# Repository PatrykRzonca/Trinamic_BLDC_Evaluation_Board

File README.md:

# Trinamic_BLDC_Evaluation_Board
Project for evaluation board

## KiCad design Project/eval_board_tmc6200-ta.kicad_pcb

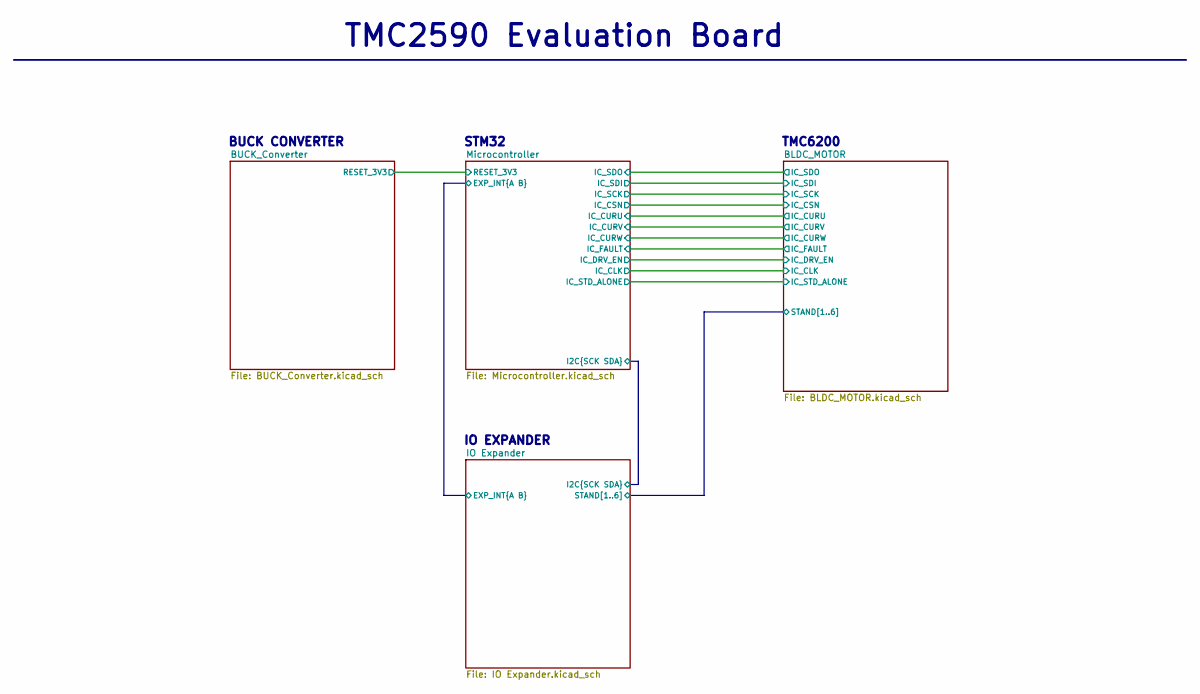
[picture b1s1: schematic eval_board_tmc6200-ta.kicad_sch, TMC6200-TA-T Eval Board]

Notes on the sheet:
BUCK CONVERTER
IO EXPANDER
TMC6200
STM32
TMC2590 Evaluation Board

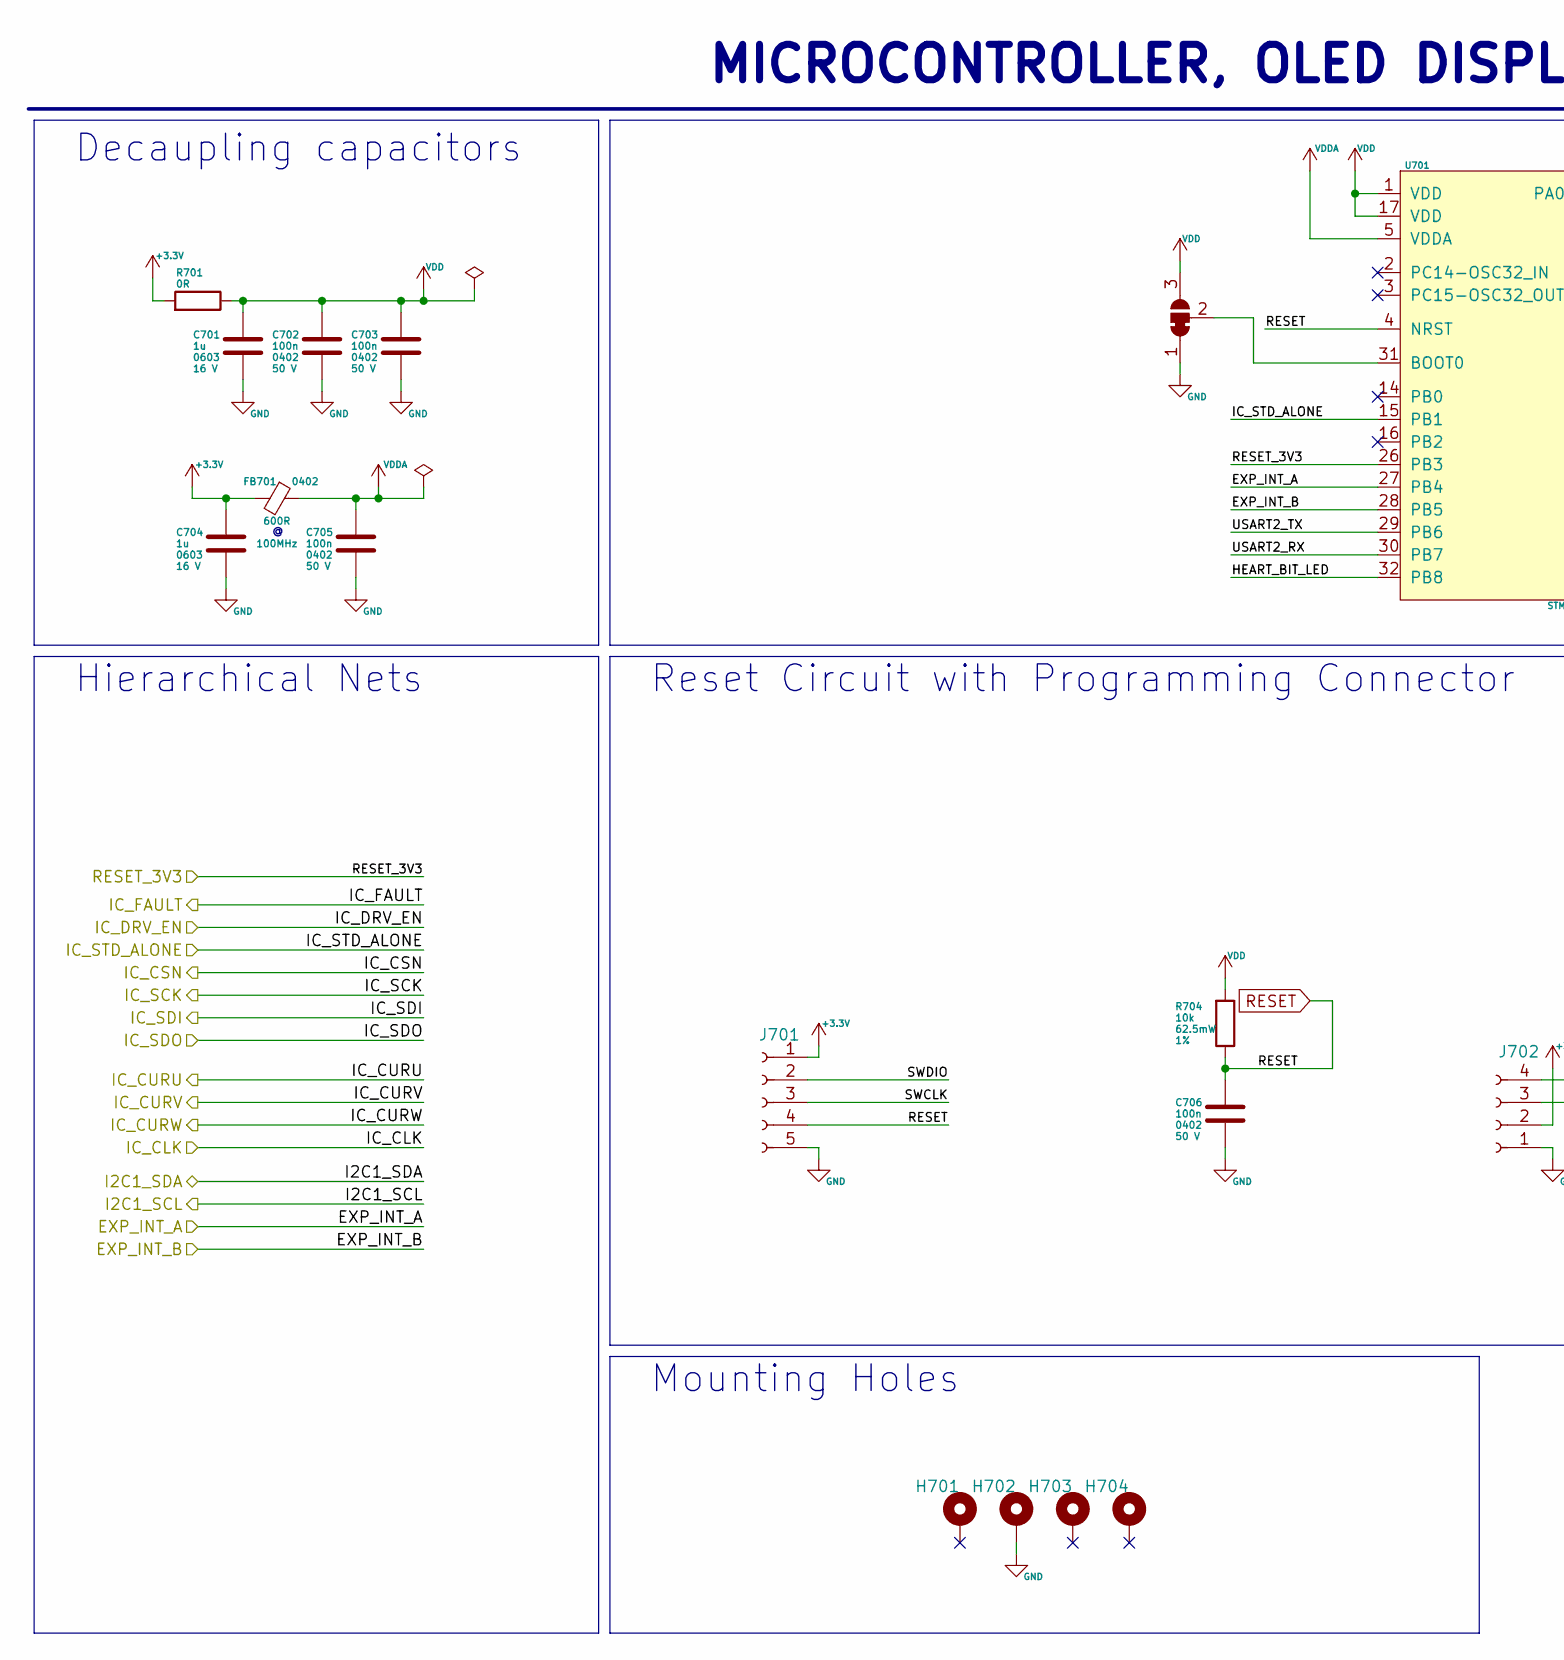
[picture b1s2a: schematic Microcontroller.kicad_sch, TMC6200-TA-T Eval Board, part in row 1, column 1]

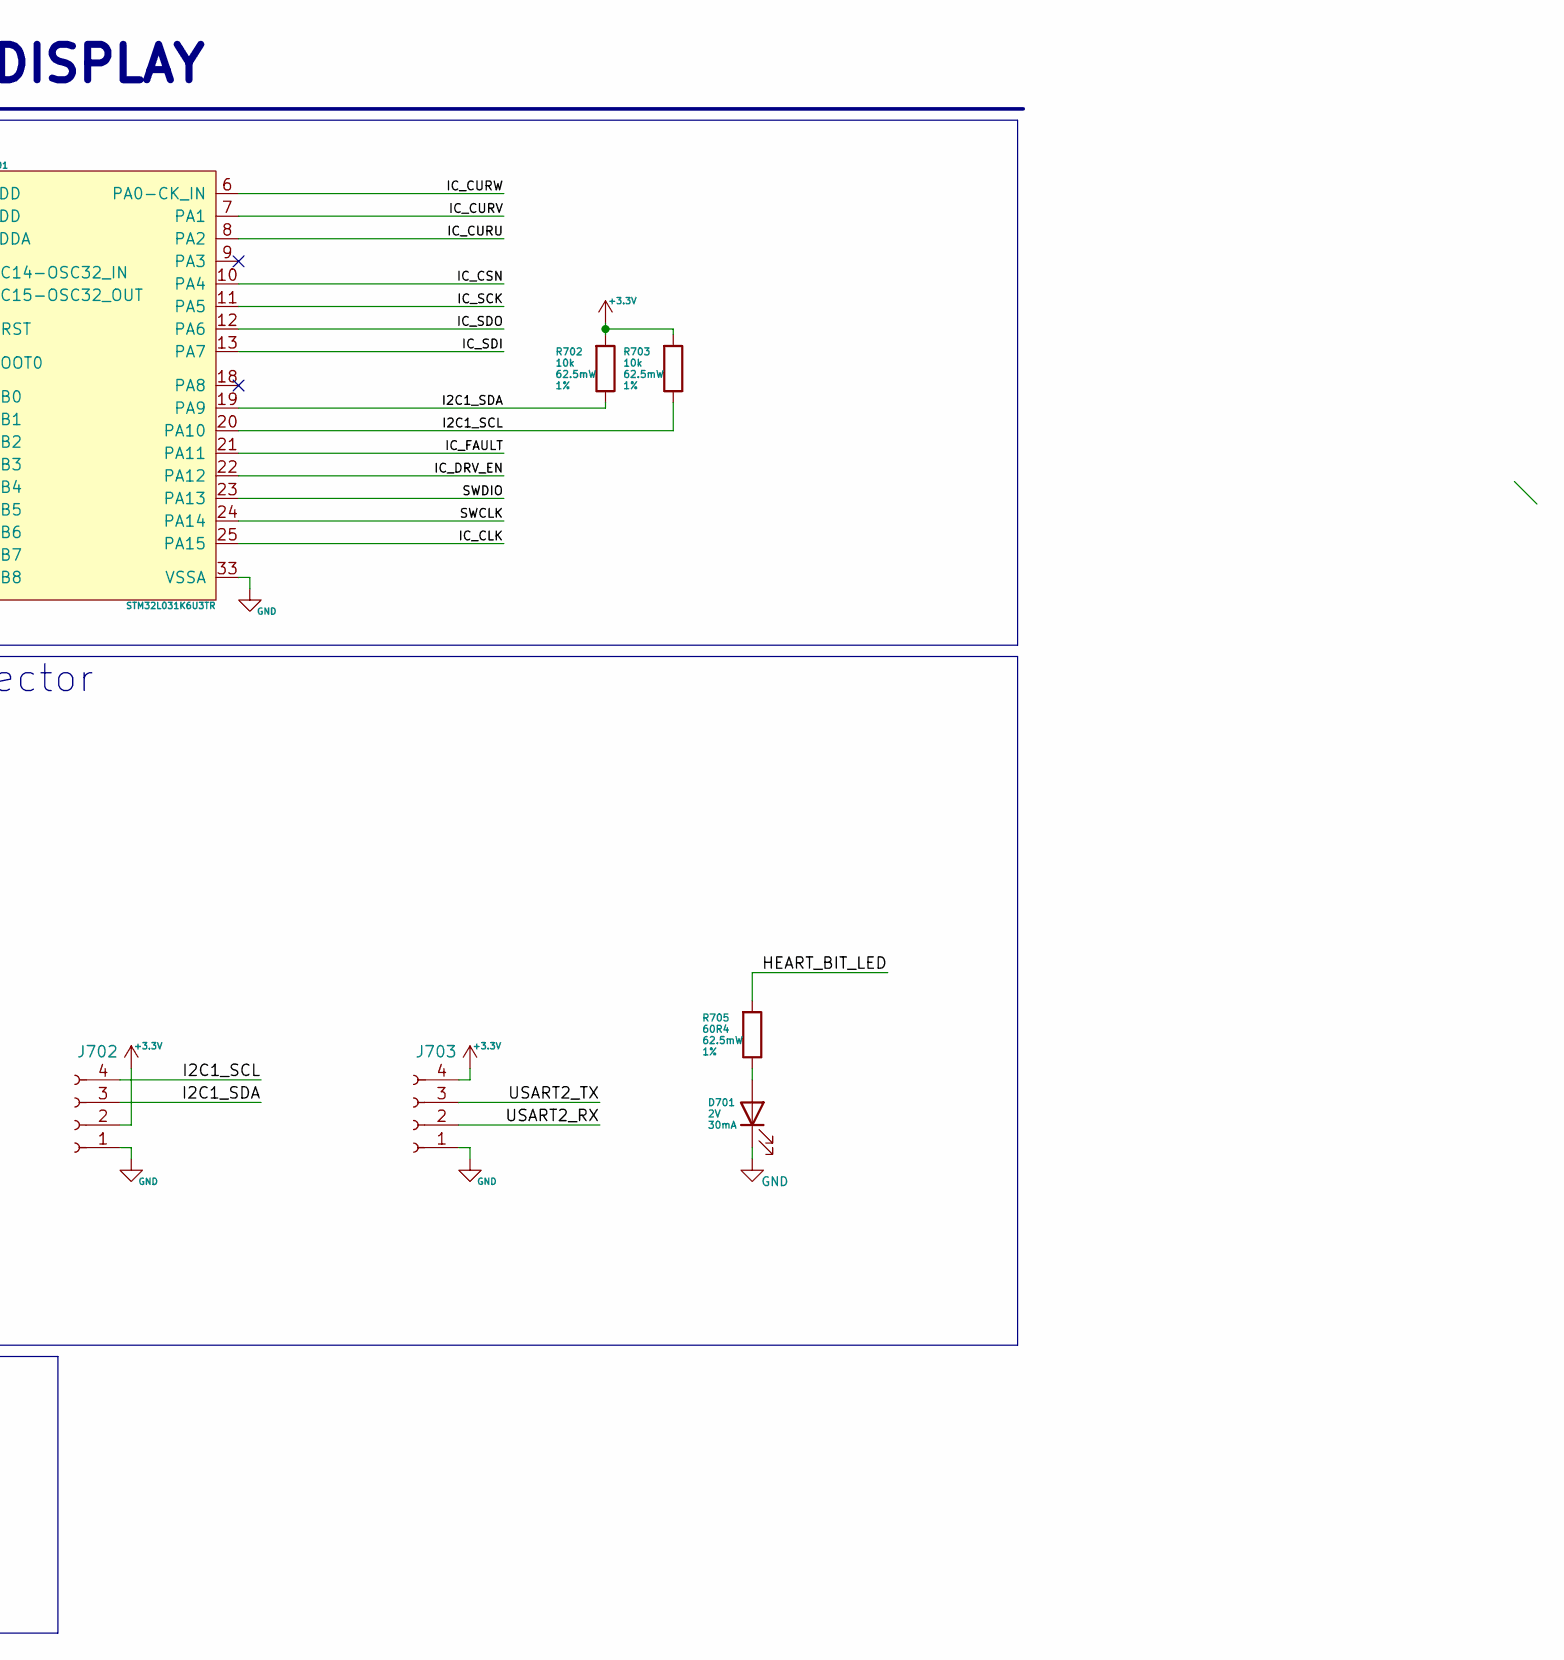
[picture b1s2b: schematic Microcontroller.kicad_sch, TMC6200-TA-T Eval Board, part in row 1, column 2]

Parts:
C701, C704: 1u; C_0603_1608Metric; Voltage 16 V; Tolerance 10 %; Part Number C0603C105K4RACTU
C702, C703, C705, C706: 100n; C_0402_1005Metric; Voltage 50 V; Tolerance 5%; Part Number GRM155C71H104JE19D
D701: LED; D_0402_1005Metric; Forward Voltage 2V; Part Number 150040VS73240
FB701: Ferrite_Bead; L_0402_1005Metric; Tolerance 25%; Part Number BLM15BD601SZ1D
H701, H702, H703, H704: MountingHole_Pad; MountingHole_2.7mm_M2.5_Pad_TopBottom
J701: Conn_01x05_Female; PinHeader_1x05_P2.54mm_Vertical
J702, J703: Conn_01x04_Female; PinHeader_1x04_P2.54mm_Vertical
JP701: SolderJumper_3_Bridged12; SolderJumper-3_P1.3mm_Bridged12_RoundedPad1.0x1.5mm_NumberL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
R701: 0R; R_0402_1005Metric; Tolerance 5%; Part Number CR0402-J/-000GLF
R702, R703, R704: 10k; R_0402_1005Metric; Tolerance 1%; Voltage 50V; Part Number RC0402FR-0710KL
R705: 60R4; R_0402_1005Metric; Tolerance 1%; Voltage 50V; Part Number RC0402FR-0760R4L
U701: STM32L031K6U3TR; STM32L031K6U3TR_UFQFPN32

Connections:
+3V3: C704.2, FB701.2, J701.1, J702.2, J703.4, R701.2, R702.2, R703.2; also elsewhere on the board
/BLDC_MOTOR/IC_CLK: U701.25 (PA15); also elsewhere on the board
/BLDC_MOTOR/IC_CSN: U701.10 (PA4); also elsewhere on the board
/BLDC_MOTOR/IC_CURU: U701.8 (PA2); also elsewhere on the board
/BLDC_MOTOR/IC_CURV: U701.7 (PA1); also elsewhere on the board
/BLDC_MOTOR/IC_CURW: U701.6 (PA0-CK_IN); also elsewhere on the board
/BLDC_MOTOR/IC_DRV_EN: U701.22 (PA12); also elsewhere on the board
/BLDC_MOTOR/IC_FAULT: U701.21 (PA11); also elsewhere on the board
/BLDC_MOTOR/IC_SCK: U701.11 (PA5); also elsewhere on the board
/BLDC_MOTOR/IC_SDI: U701.13 (PA7); also elsewhere on the board
/BLDC_MOTOR/IC_SDO: U701.12 (PA6); also elsewhere on the board
/BLDC_MOTOR/IC_STD_ALONE: U701.15 (PB1); also elsewhere on the board
/IO Expander/EXP_INT_1: U701.27 (PB4); also elsewhere on the board
/IO Expander/EXP_INT_2: U701.28 (PB5); also elsewhere on the board
/Microcontroller/HEART_BIT_LED: R705.2, U701.32 (PB8)
/Microcontroller/RESET: C706.1, J701.4, R704.1, U701.4 (NRST)
/Microcontroller/RESET_3V3: U701.26 (PB3); also elsewhere on the board
/Microcontroller/SWCLK: J701.3, U701.24 (PA14)
/Microcontroller/SWDIO: J701.2, U701.23 (PA13)
/Microcontroller/USART2_RX: J703.2, U701.30 (PB7)
/Microcontroller/USART2_TX: J703.3, U701.29 (PB6)
GND: C701.1, C702.2, C703.2, C704.1, C705.2, C706.2, D701.1 (K), H702.1, J701.5, J702.1, J703.1, JP701.1 (A), U701.33 (VSSA); also elsewhere on the board
unnamed: D701.2 (A), R705.1
unnamed: JP701.2 (C), U701.31 (BOOT0)
VDD: C701.2, C702.1, C703.1, JP701.3 (B), R701.1, R704.2, U701.1 (VDD), U701.17 (VDD); also elsewhere on the board
VDDA: C705.1, FB701.1, U701.5 (VDDA)

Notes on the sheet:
Reset Circuit with Programming Connector
Hierarchical Nets
Decaupling capacitors
MICROCONTROLLER, OLED DISPLAY
Mounting Holes

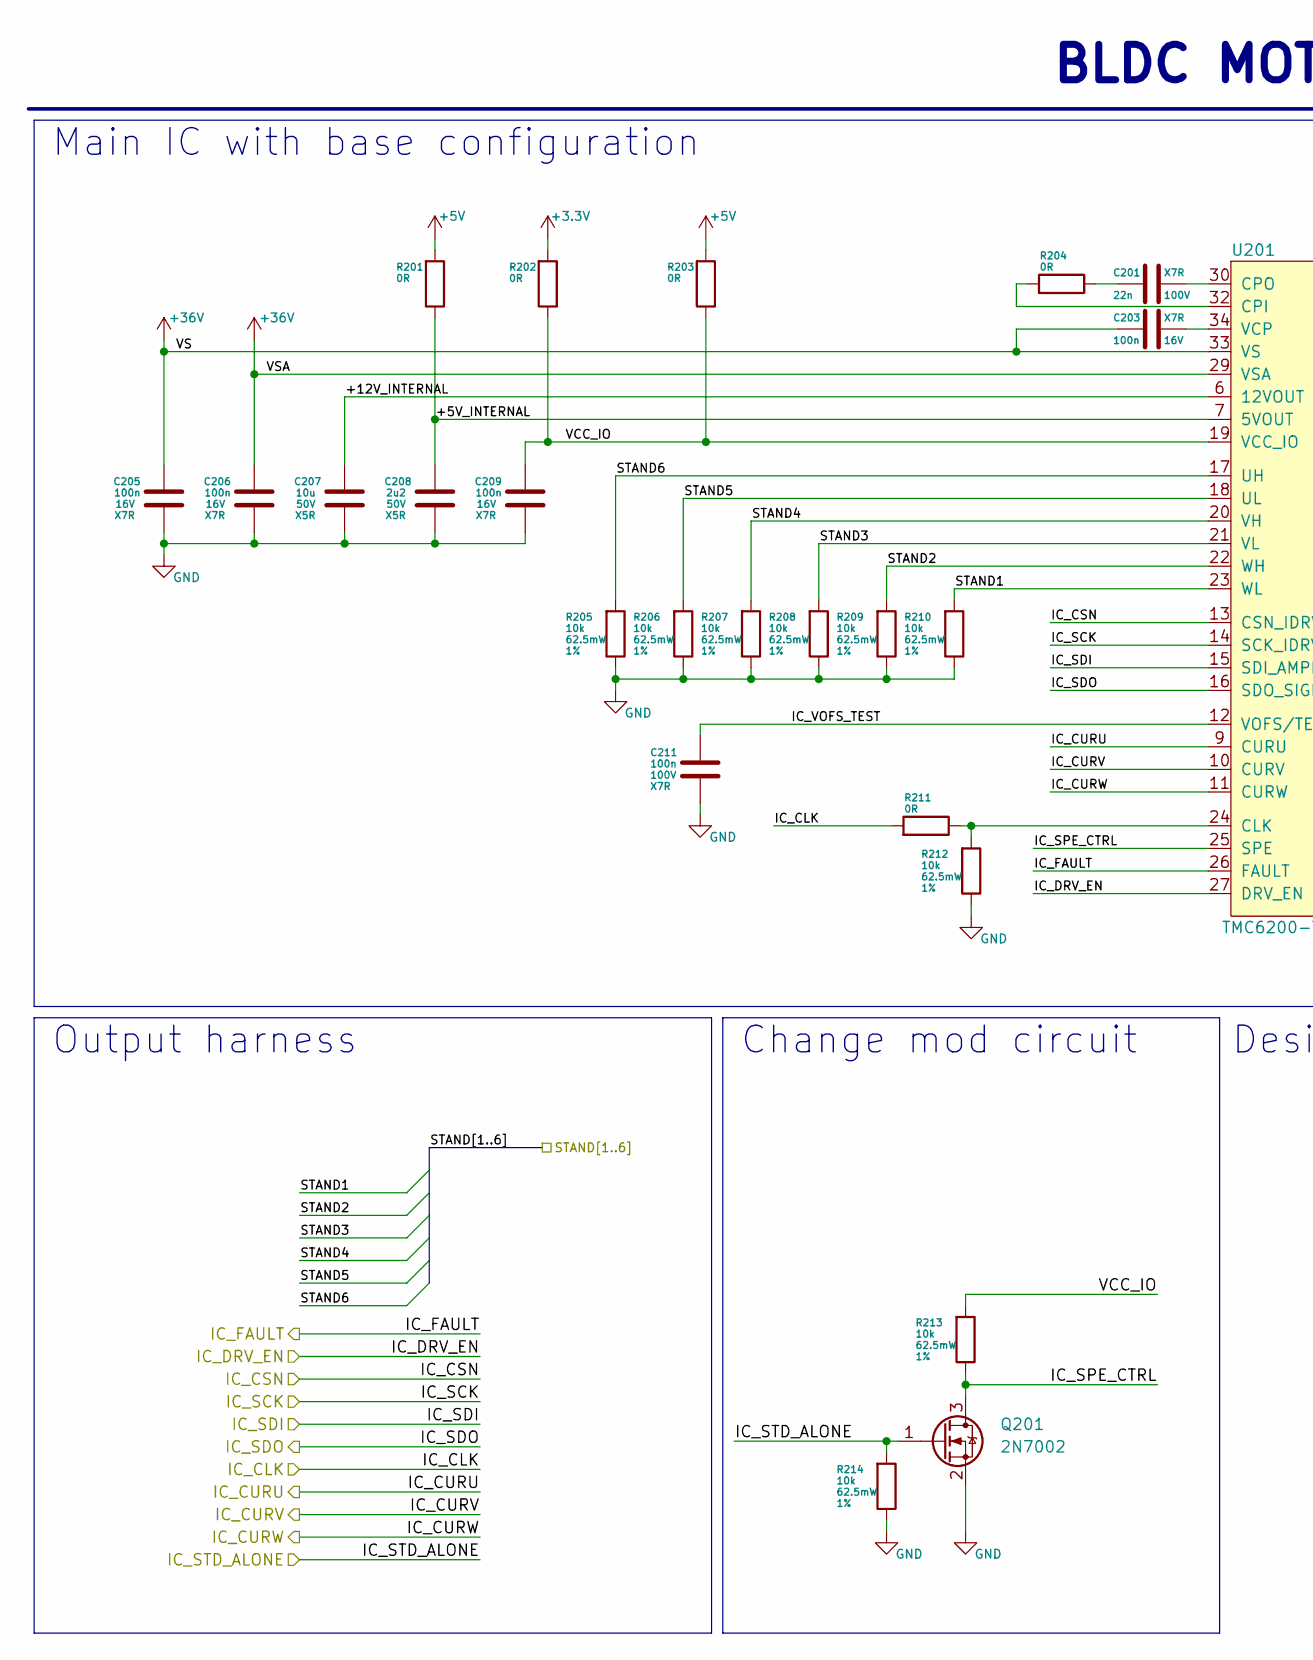
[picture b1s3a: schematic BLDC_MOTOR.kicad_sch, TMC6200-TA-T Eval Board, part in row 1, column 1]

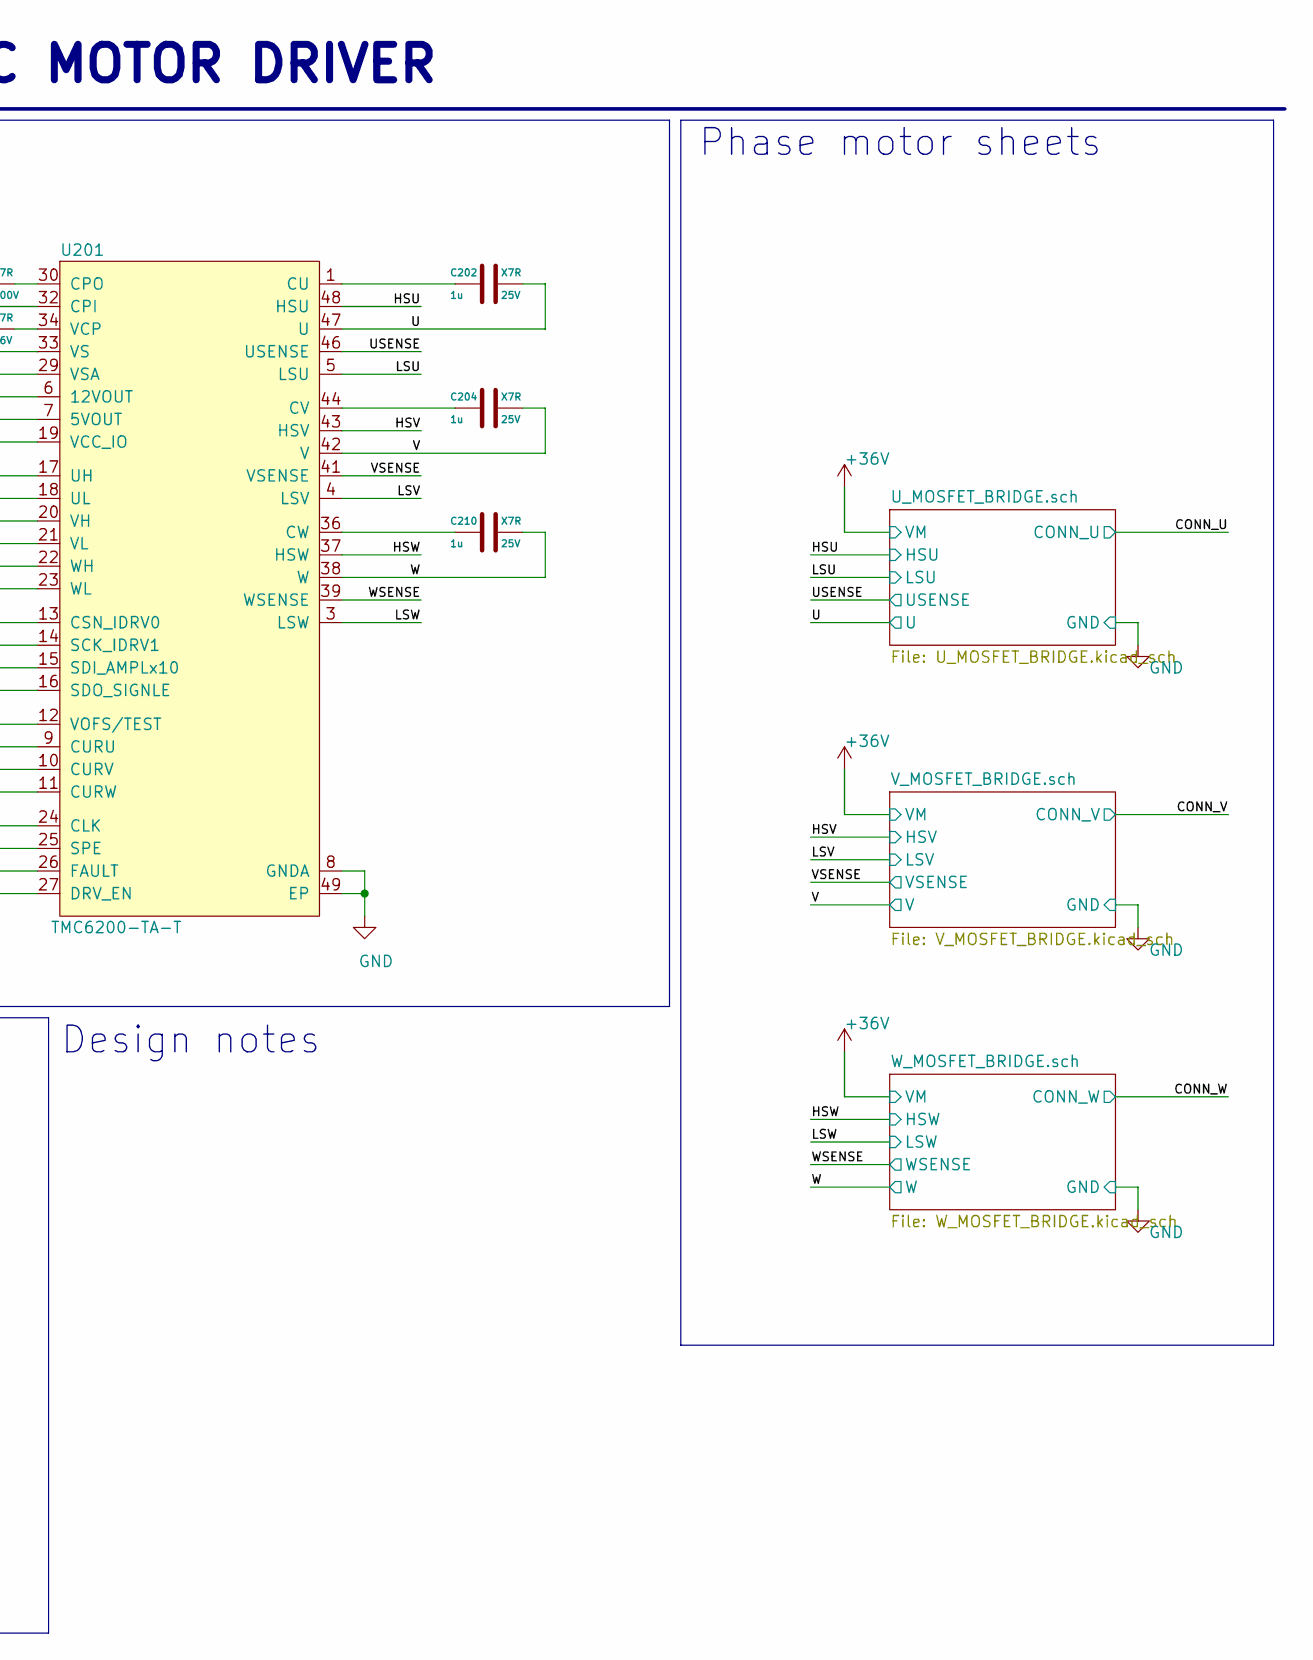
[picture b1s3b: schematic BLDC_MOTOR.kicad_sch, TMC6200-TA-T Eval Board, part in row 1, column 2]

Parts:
C201: 22n; C_0603_1608Metric; DC Voltage 100V; Tolerance 10%; Part Number CGA3E2X7R2A223K080AA
C202, C204, C210: 1u; C_0603_1608Metric; DC Voltage 25V; Tolerance 10%; Part Number CL10B105KA8NNNL
C203, C205, C206, C209: 100n; C_0603_1608Metric; DC Voltage 16V; Tolerance 10%; Part Number EMK107B7104KA-T
C207: 10u; C_1206_3216Metric; DC Voltage 50V; Tolerance 10%; Part Number UMK316BBJ106KL-T
C208: 2u2; C_0603_1608Metric; DC Voltage 50V; Tolerance 10%; Part Number UMK107BBJ225KA-T
C211: 100n; C_0603_1608Metric; DC Voltage 100V; Tolerance 5%; Part Number CL10B104JB8NNNC
Q201: 2N7002; SOT-23
R201, R202, R203, R211: 0R; R_0402_1005Metric; Tolerance 5%; Part Number CR0402-J/-000GLF
R204: 0R; R_0603_1608Metric; Part Number CR0603-J/-000ELF
R205, R206, R207, R208, R209, R210, R212, R213, R214: 10k; R_0402_1005Metric; Tolerance 1%; Voltage 50V; Part Number RC0402FR-0710KL
U201: TMC6200-TA-T; TMC6200-TA_eTQFP47

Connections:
+3V3: R202.2; also elsewhere on the board
+5V: R201.2, R203.2; also elsewhere on the board
+36V: C203.1, C205.1, C206.1, U201.29 (VSA), U201.33 (VS); also elsewhere on the board
/BLDC_MOTOR/+5V_INTERNAL: C208.1, R201.1, U201.7 (5VOUT)
/BLDC_MOTOR/+12V_INTERNAL: C207.1, U201.6 (12VOUT)
/BLDC_MOTOR/HSU: U201.48 (HSU); also elsewhere on the board
/BLDC_MOTOR/HSV: U201.43 (HSV); also elsewhere on the board
/BLDC_MOTOR/HSW: U201.37 (HSW); also elsewhere on the board
/BLDC_MOTOR/IC_CLK: R211.2; also elsewhere on the board
/BLDC_MOTOR/IC_CSN: U201.13 (CSN_IDRV0); also elsewhere on the board
/BLDC_MOTOR/IC_CURU: U201.9 (CURU); also elsewhere on the board
/BLDC_MOTOR/IC_CURV: U201.10 (CURV); also elsewhere on the board
/BLDC_MOTOR/IC_CURW: U201.11 (CURW); also elsewhere on the board
/BLDC_MOTOR/IC_DRV_EN: U201.27 (DRV_EN); also elsewhere on the board
/BLDC_MOTOR/IC_FAULT: U201.26 (FAULT); also elsewhere on the board
/BLDC_MOTOR/IC_SCK: U201.14 (SCK_IDRV1); also elsewhere on the board
/BLDC_MOTOR/IC_SDI: U201.15 (SDI_AMPLx10); also elsewhere on the board
/BLDC_MOTOR/IC_SDO: U201.16 (SDO_SIGNLE); also elsewhere on the board
/BLDC_MOTOR/IC_SPE_CTRL: Q201.3 (D), R213.1, U201.25 (SPE)
/BLDC_MOTOR/IC_STD_ALONE: Q201.1 (G), R214.2; also elsewhere on the board
/BLDC_MOTOR/IC_VOFS_TEST: C211.1, U201.12 (VOFS/TEST)
/BLDC_MOTOR/LSU: U201.5 (LSU); also elsewhere on the board
/BLDC_MOTOR/LSV: U201.4 (LSV); also elsewhere on the board
/BLDC_MOTOR/LSW: U201.3 (LSW); also elsewhere on the board
/BLDC_MOTOR/STAND1: R210.2, U201.23 (WL); also elsewhere on the board
/BLDC_MOTOR/STAND2: R209.2, U201.22 (WH); also elsewhere on the board
/BLDC_MOTOR/STAND3: R208.2, U201.21 (VL); also elsewhere on the board
/BLDC_MOTOR/STAND4: R207.2, U201.20 (VH); also elsewhere on the board
/BLDC_MOTOR/STAND5: R206.2, U201.18 (UL); also elsewhere on the board
/BLDC_MOTOR/STAND6: R205.2, U201.17 (UH); also elsewhere on the board
/BLDC_MOTOR/U: C202.2, U201.47 (U); also elsewhere on the board
/BLDC_MOTOR/USENSE: U201.46 (USENSE); also elsewhere on the board
/BLDC_MOTOR/V: C204.2, U201.42 (V); also elsewhere on the board
/BLDC_MOTOR/VCC_IO: C209.1, R202.1, R203.1, R213.2, U201.19 (VCC_IO)
/BLDC_MOTOR/VSENSE: U201.41 (VSENSE); also elsewhere on the board
/BLDC_MOTOR/W: C210.2, U201.38 (W); also elsewhere on the board
/BLDC_MOTOR/WSENSE: U201.39 (WSENSE); also elsewhere on the board
GND: C205.2, C206.2, C207.2, C208.2, C209.2, C211.2, Q201.2 (S), R205.1, R206.1, R207.1, R208.1, R209.1, R210.1, R212.1, R214.1, U201.8 (GNDA), U201.49 (EP); also elsewhere on the board
unnamed: C201.1, R204.1
unnamed: C201.2, U201.30 (CPO)
unnamed: C202.1, U201.1 (CU)
unnamed: C203.2, U201.34 (VCP)
unnamed: C204.1, U201.44 (CV)
unnamed: C210.1, U201.36 (CW)
unnamed: R204.2, U201.32 (CPI)
unnamed: R211.1, R212.2, U201.24 (CLK)

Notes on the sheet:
Output harness
Main IC with base configuration
Design notes
Phase motor sheets
BLDC MOTOR DRIVER
Change mod circuit

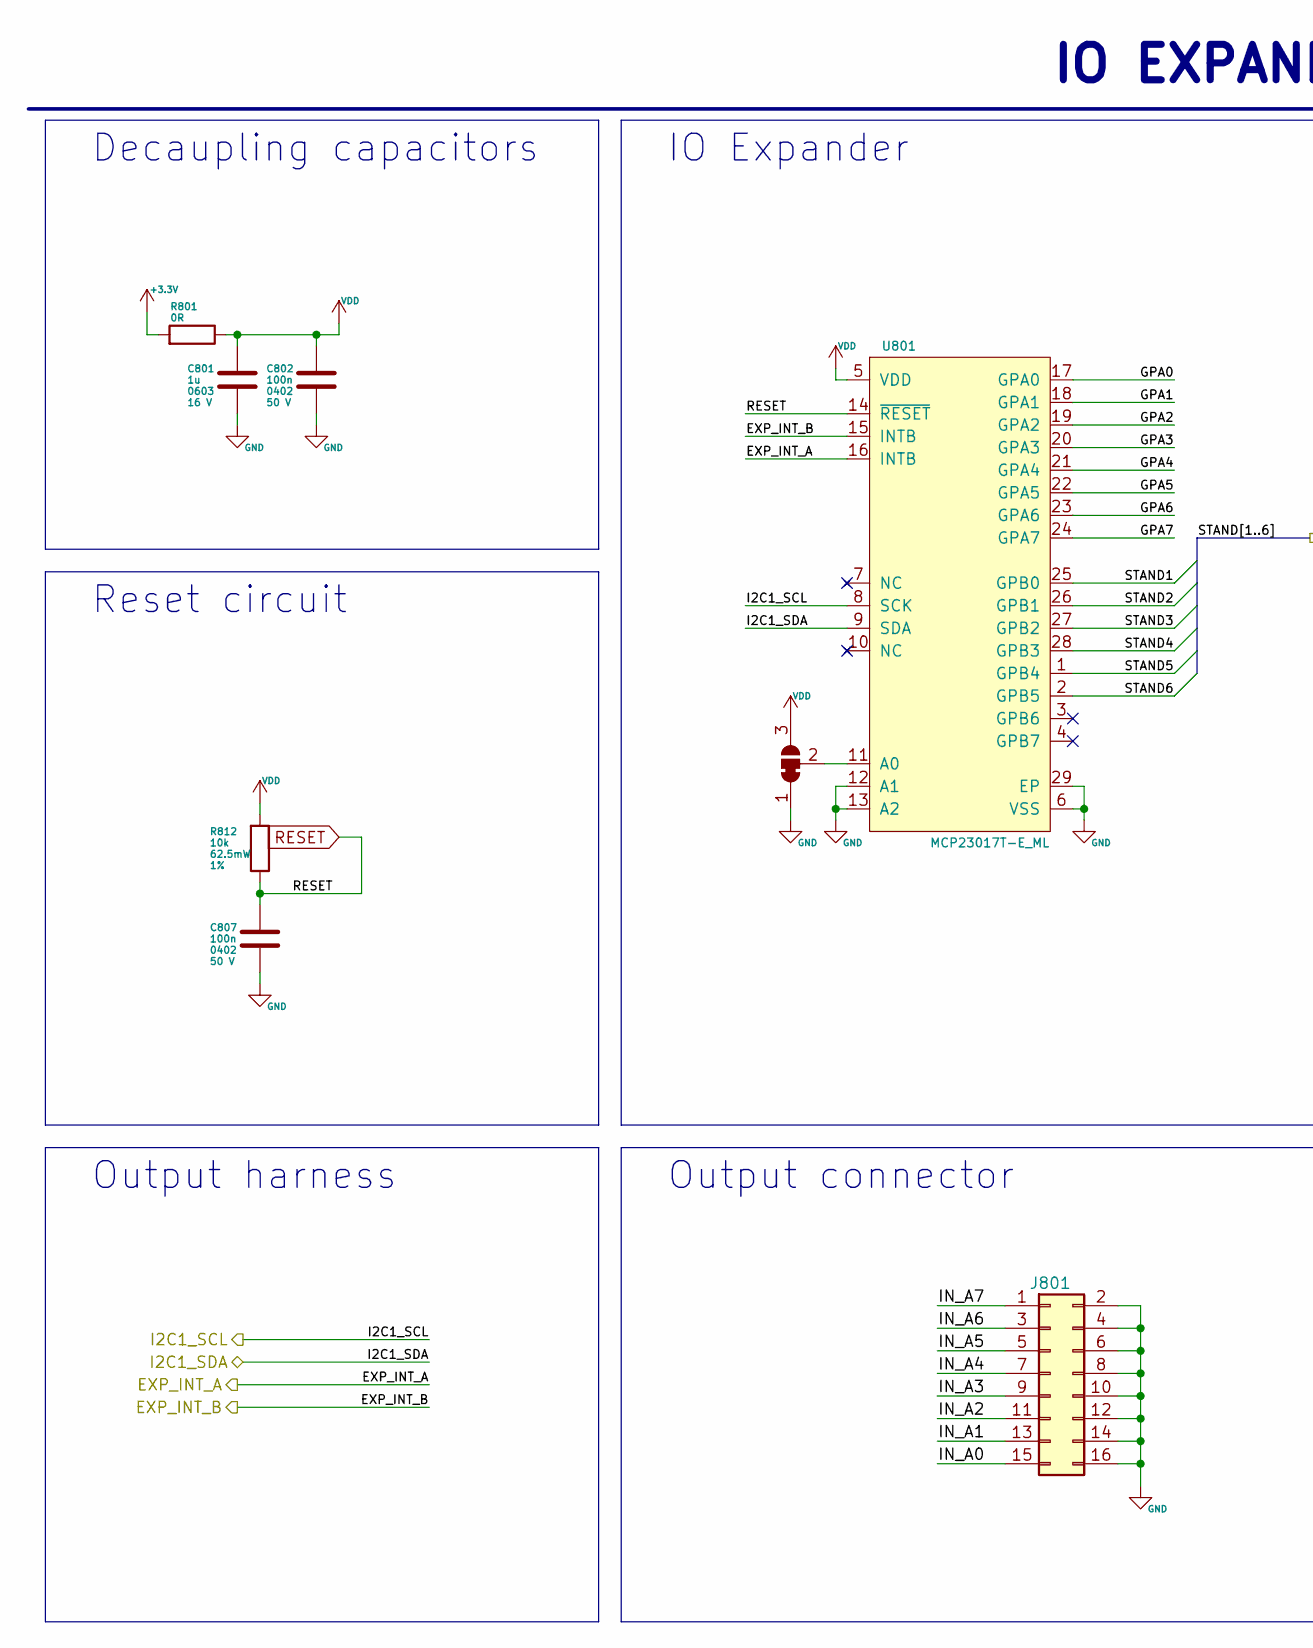
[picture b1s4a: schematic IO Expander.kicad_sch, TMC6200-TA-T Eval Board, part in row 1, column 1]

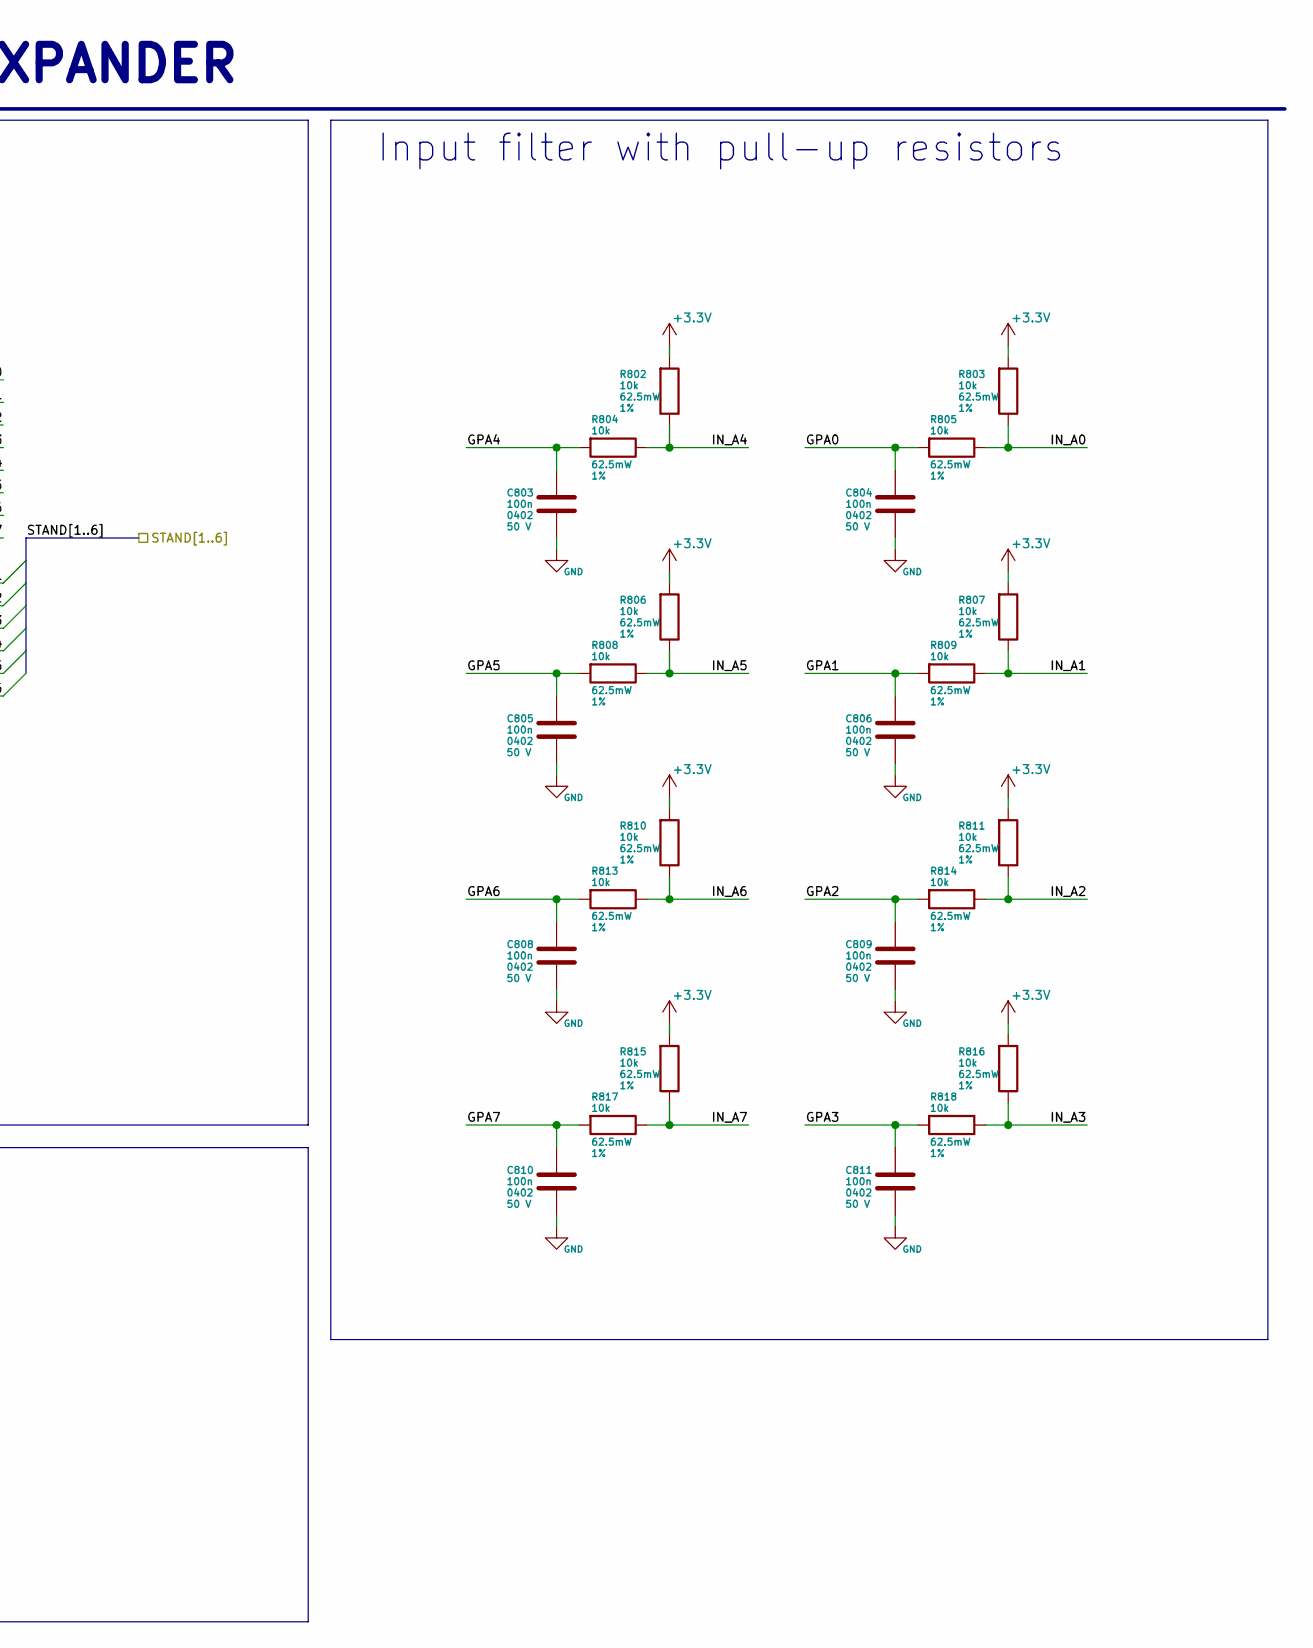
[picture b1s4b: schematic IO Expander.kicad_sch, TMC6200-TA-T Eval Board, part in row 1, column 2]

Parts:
C801: 1u; C_0603_1608Metric; Voltage 16 V; Tolerance 10 %; Part Number C0603C105K4RACTU
C802, C803, C804, C805, C806, C807, C808, C809, C810, C811: 100n; C_0402_1005Metric; Voltage 50 V; Tolerance 5%; Part Number GRM155C71H104JE19D
J801: Conn_02x08_Odd_Even; PinHeader_2x08_P2.54mm_Vertical
JP801: SolderJumper_3_Bridged12; SolderJumper-3_P1.3mm_Bridged12_RoundedPad1.0x1.5mm_NumberL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
R801: 0R; R_0402_1005Metric; Tolerance 5%; Part Number CR0402-J/-000GLF
R802, R803, R804, R805, R806, R807, R808, R809, R810, R811, R812, R813, R814, R815, R816, R817, R818: 10k; R_0402_1005Metric; Tolerance 1%; Voltage 50V; Part Number RC0402FR-0710KL
U801: MCP23017T-E_ML; MCP23017T-EML_QFN-28

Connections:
+3V3: R801.2, R802.2, R803.2, R806.2, R807.2, R810.2, R811.2, R815.2, R816.2; also elsewhere on the board
/BLDC_MOTOR/STAND1: U801.25 (GPB0); also elsewhere on the board
/BLDC_MOTOR/STAND2: U801.26 (GPB1); also elsewhere on the board
/BLDC_MOTOR/STAND3: U801.27 (GPB2); also elsewhere on the board
/BLDC_MOTOR/STAND4: U801.28 (GPB3); also elsewhere on the board
/BLDC_MOTOR/STAND5: U801.1 (GPB4); also elsewhere on the board
/BLDC_MOTOR/STAND6: U801.2 (GPB5); also elsewhere on the board
/IO Expander/EXP_INT_1: U801.16 (INTA); also elsewhere on the board
/IO Expander/EXP_INT_2: U801.15 (INTB); also elsewhere on the board
/IO Expander/GPA0: C804.1, R805.2, U801.17 (GPA0)
/IO Expander/GPA1: C806.1, R809.2, U801.18 (GPA1)
/IO Expander/GPA2: C809.1, R814.2, U801.19 (GPA2)
/IO Expander/GPA3: C811.1, R818.2, U801.20 (GPA3)
/IO Expander/GPA4: C803.1, R804.2, U801.21 (GPA4)
/IO Expander/GPA5: C805.1, R808.2, U801.22 (GPA5)
/IO Expander/GPA6: C808.1, R813.2, U801.23 (GPA6)
/IO Expander/GPA7: C810.1, R817.2, U801.24 (GPA7)
/IO Expander/I2C1: U801.8 (SCK)
/IO Expander/I2C2: U801.9 (SDA)
/IO Expander/IN_A0: J801.15, R803.1, R805.1
/IO Expander/IN_A1: J801.13, R807.1, R809.1
/IO Expander/IN_A2: J801.11, R811.1, R814.1
/IO Expander/IN_A3: J801.9, R816.1, R818.1
/IO Expander/IN_A4: J801.7, R802.1, R804.1
/IO Expander/IN_A5: J801.5, R806.1, R808.1
/IO Expander/IN_A6: J801.3, R810.1, R813.1
/IO Expander/IN_A7: J801.1, R815.1, R817.1
GND: C801.1, C802.2, C803.2, C804.2, C805.2, C806.2, C807.2, C808.2, C809.2, C810.2, C811.2, J801.2, J801.4, J801.6, J801.8, J801.10, J801.12, J801.14, J801.16, JP801.1 (A), U801.6 (VSS), U801.12 (A1), U801.13 (A2), U801.29 (EP); also elsewhere on the board
unnamed: JP801.2 (C), U801.11 (A0)
RESET: C807.1, R812.1, U801.14 (~RESET)
VDD: C801.2, C802.1, JP801.3 (B), R801.1, R812.2, U801.5 (VDD); also elsewhere on the board

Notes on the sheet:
Reset circuit
Input filter with pull-up resistors
IO EXPANDER
IO Expander
Output harness
Decaupling capacitors
Output connector
